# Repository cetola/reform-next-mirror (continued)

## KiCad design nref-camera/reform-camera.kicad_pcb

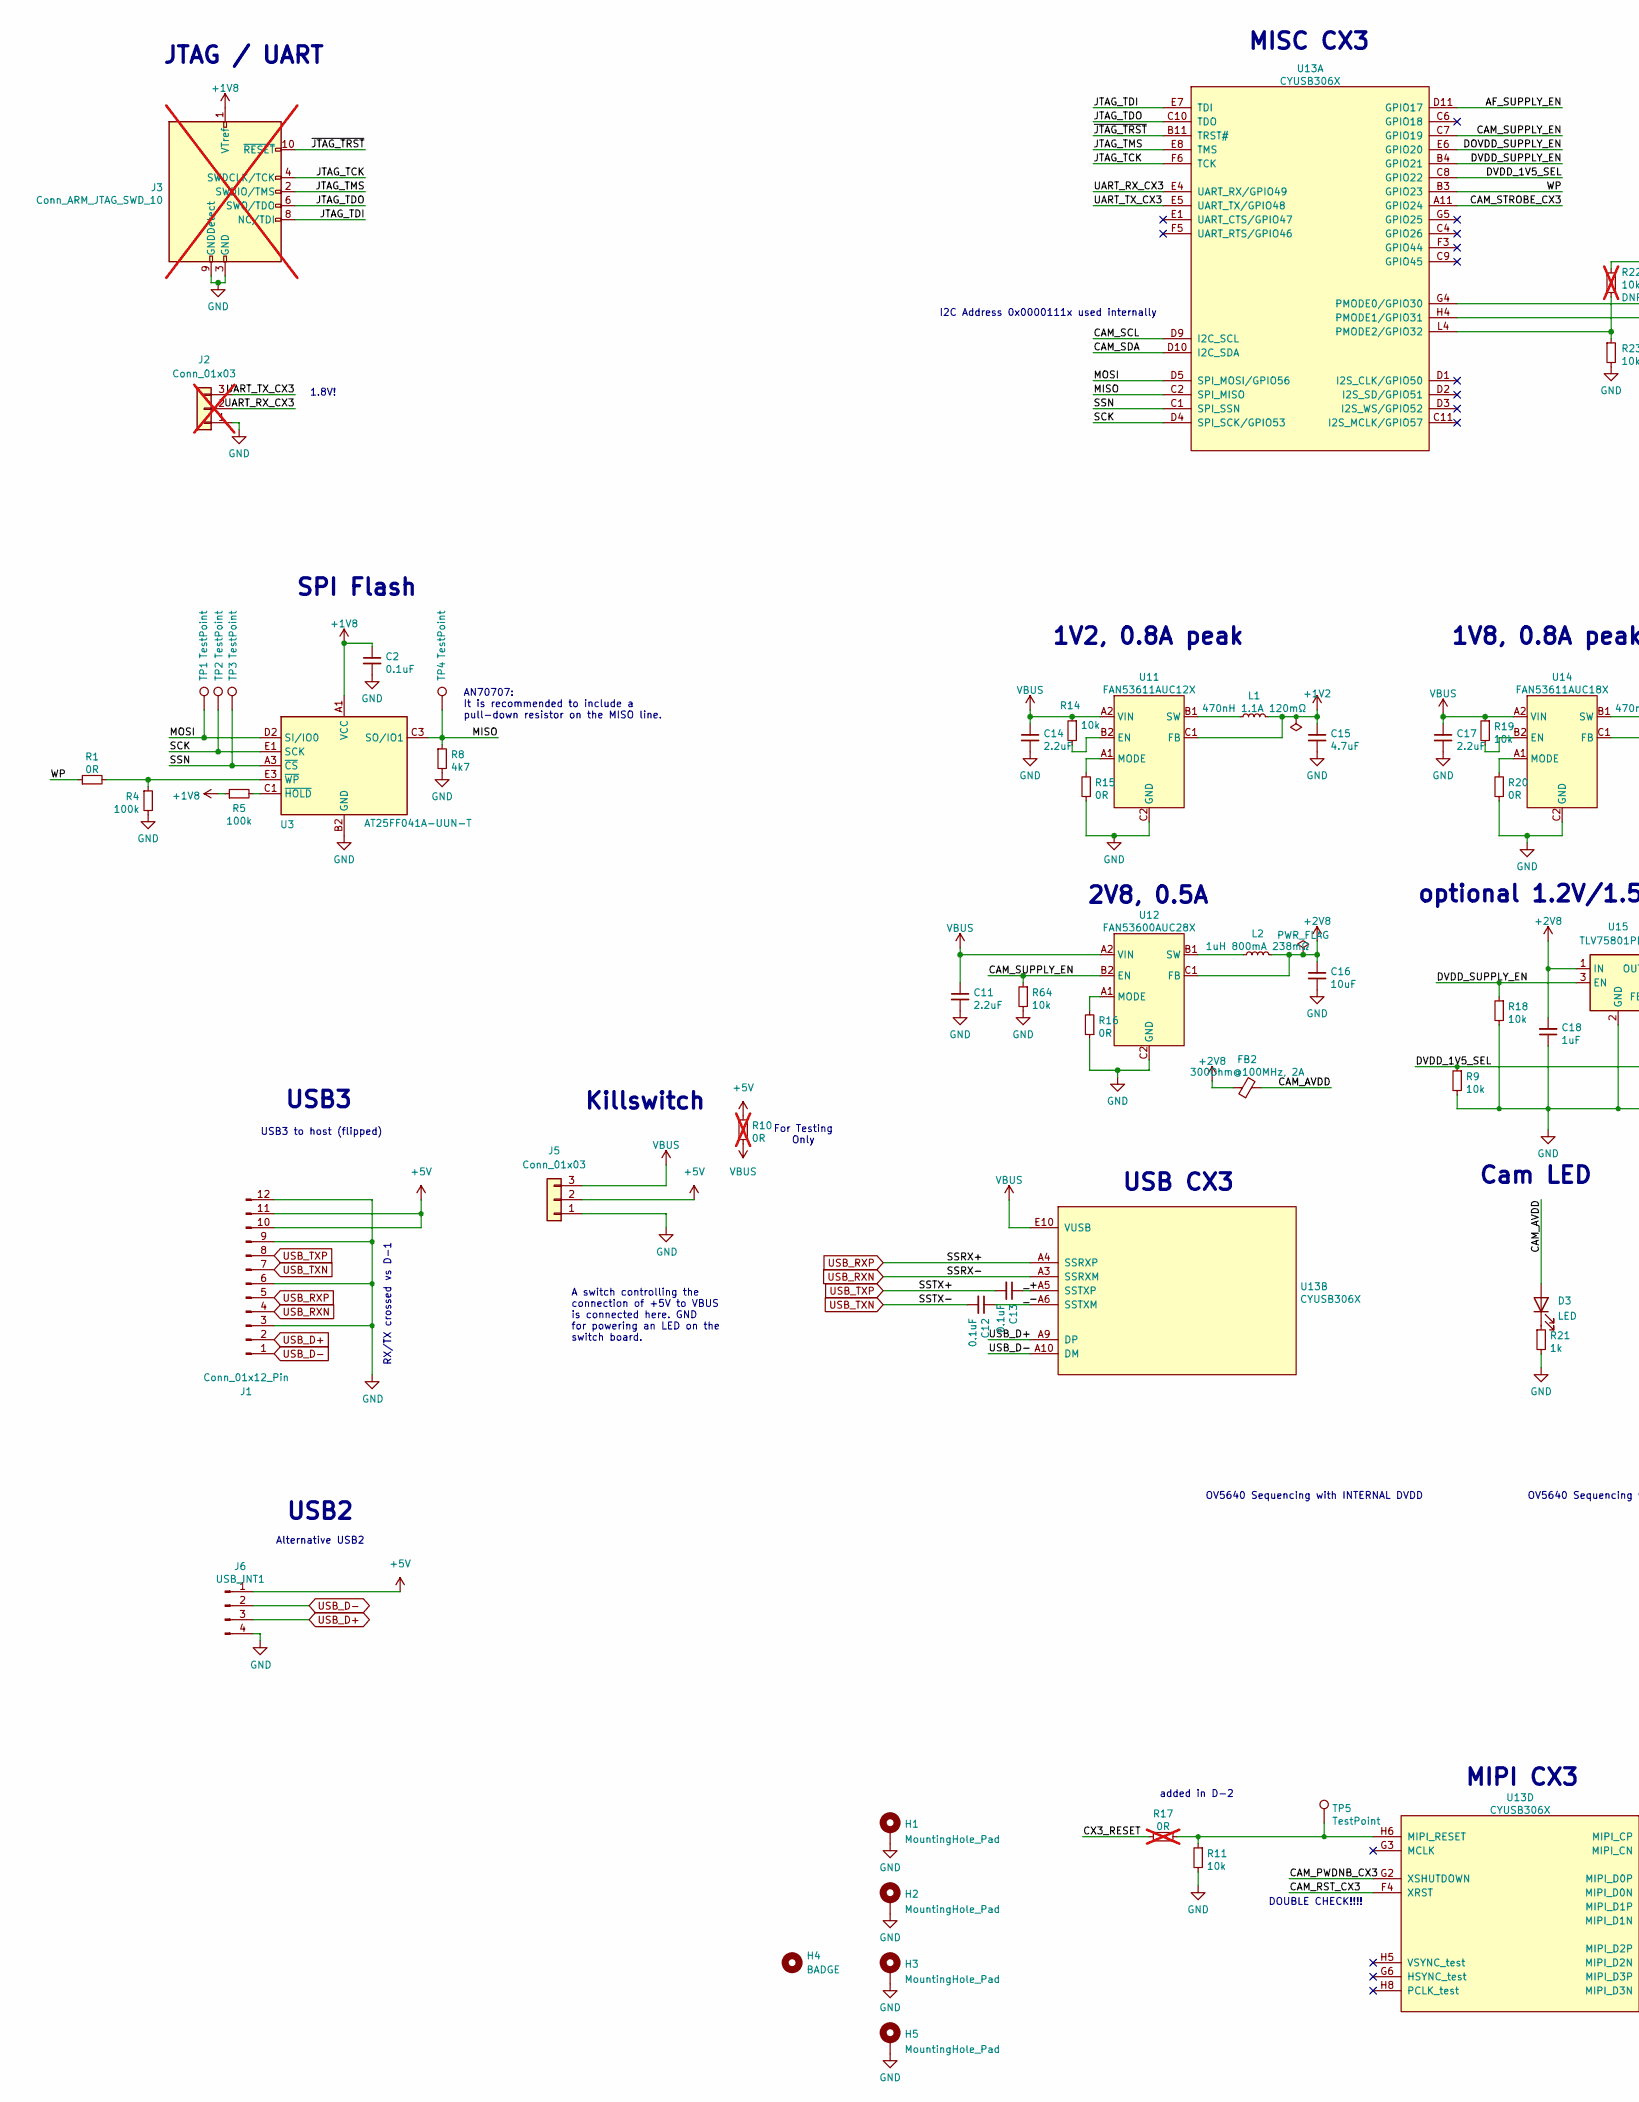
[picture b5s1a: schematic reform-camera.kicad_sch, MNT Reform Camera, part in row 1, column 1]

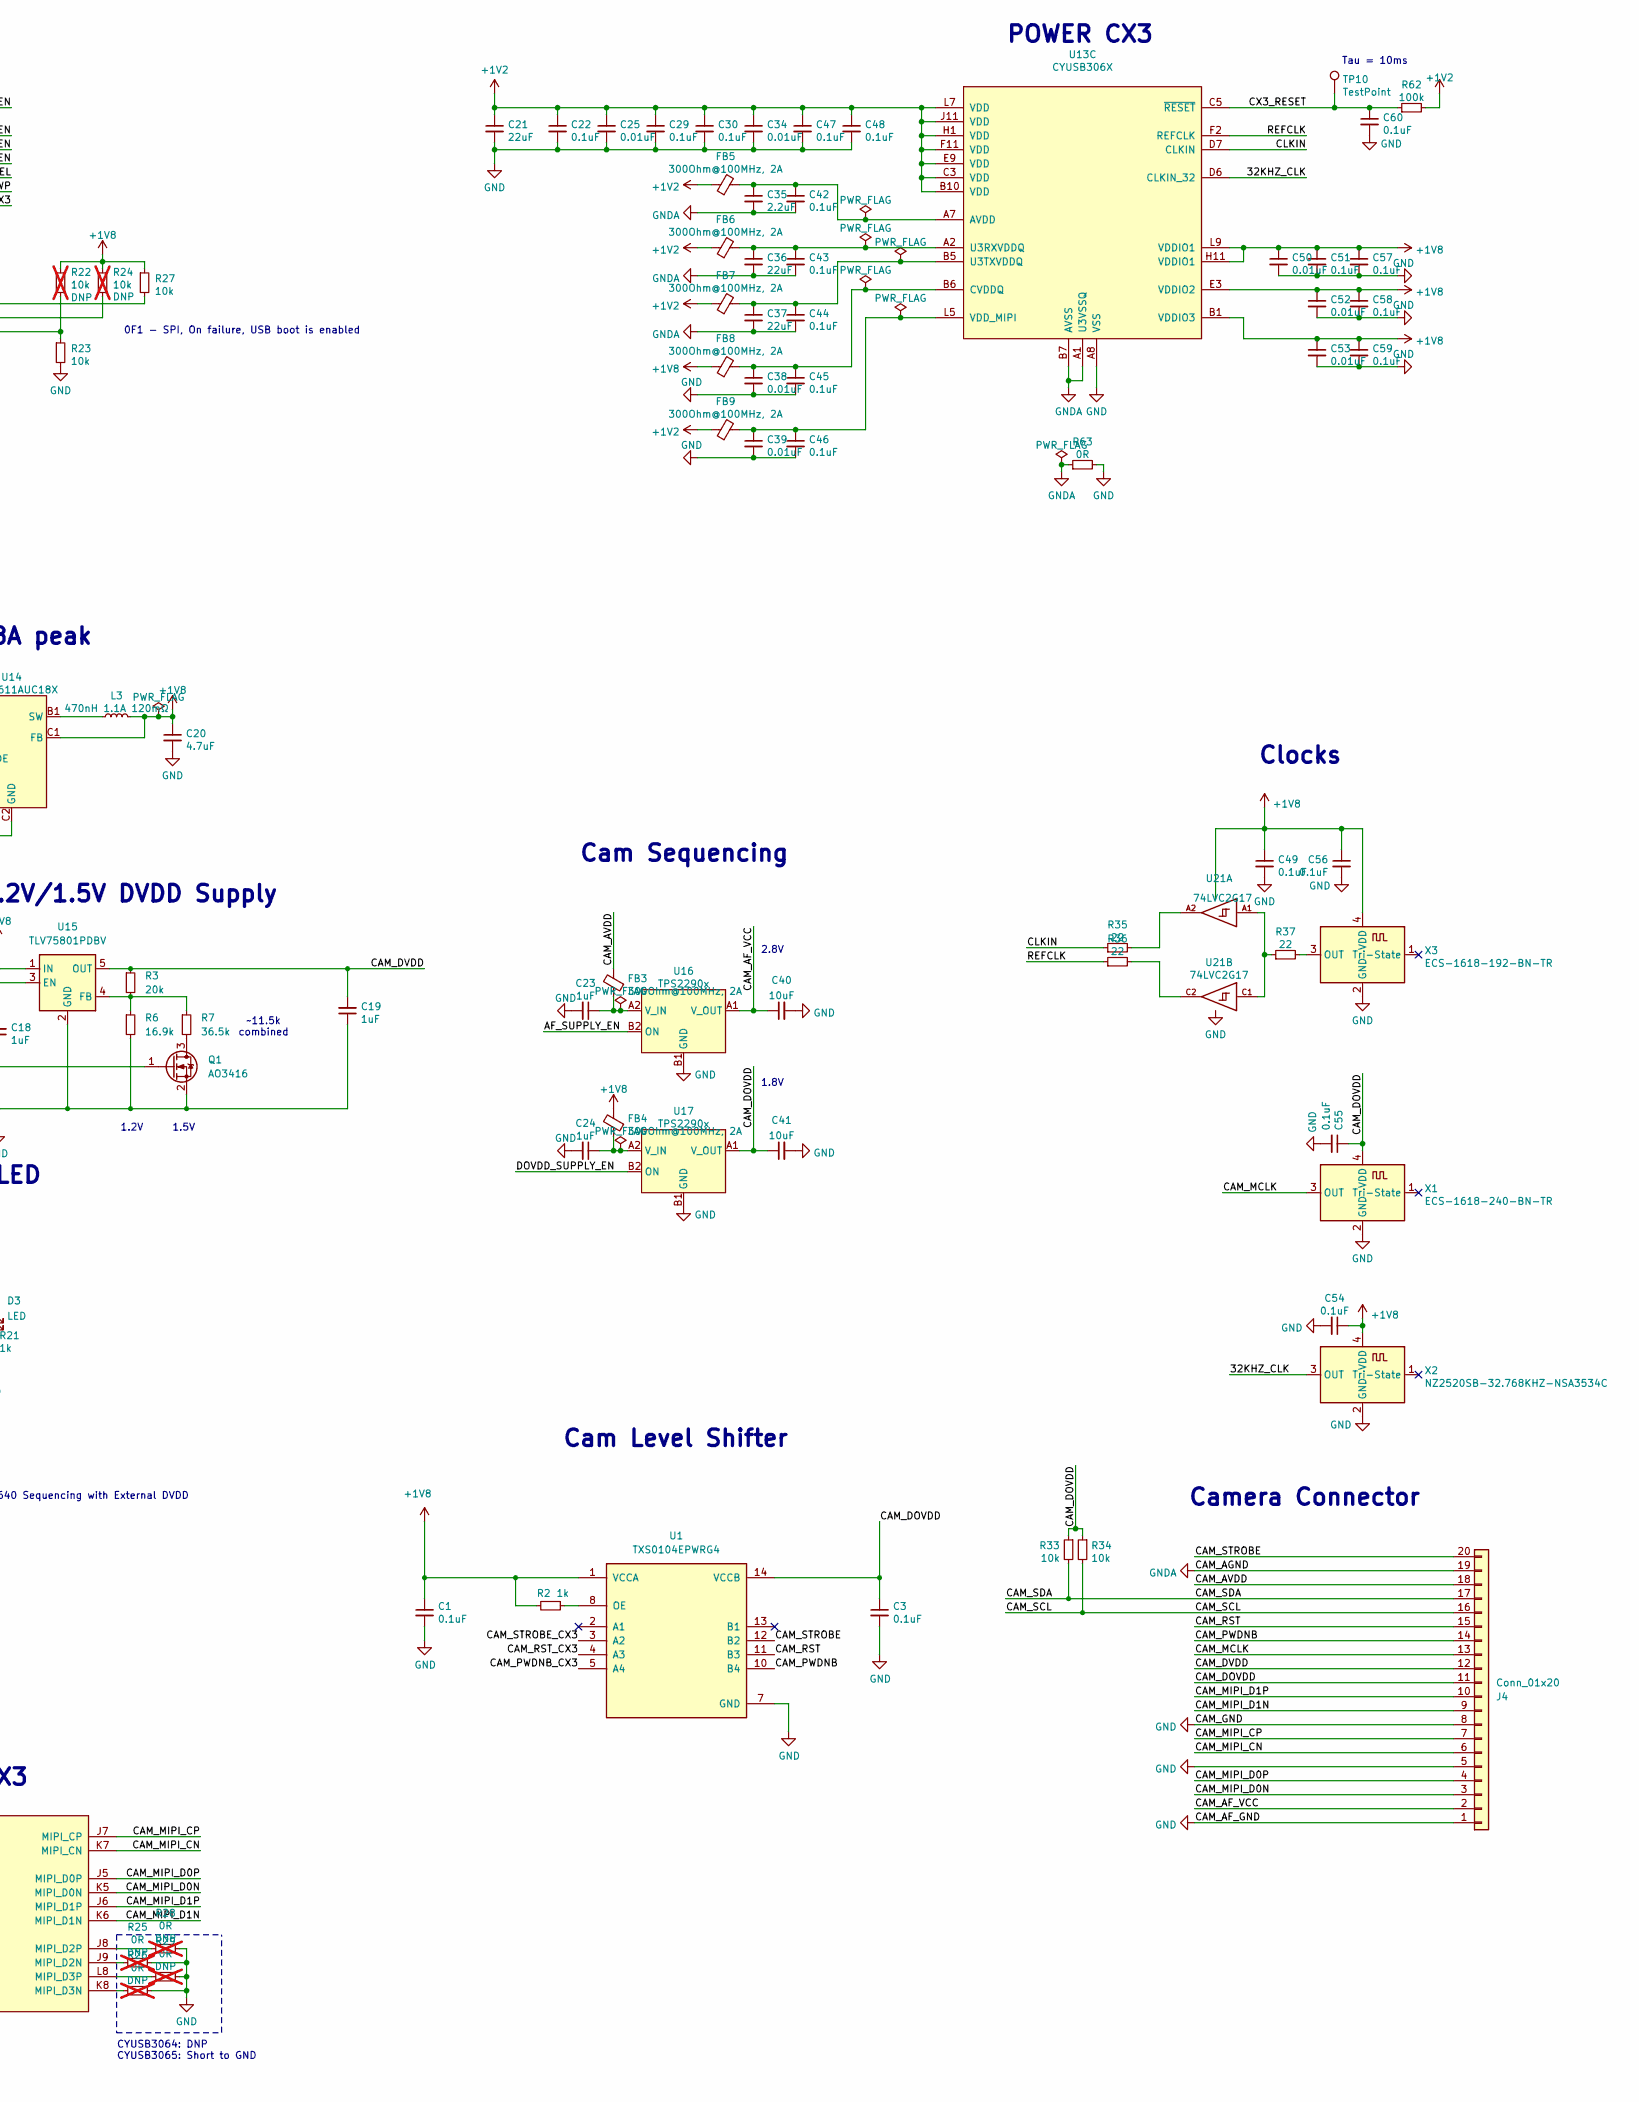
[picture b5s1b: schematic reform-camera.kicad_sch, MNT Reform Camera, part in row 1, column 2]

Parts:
C1, C3: 0.1uF; C_0402_1005Metric; MPN GRM155R71C104KA88J; LCSC C60474
C2, C12, C13, C22, C29, C30, C42, C43, C44, C45, C46, C47, C48, C49, C51, C54, C55, C56, C57, C58, C59, C60: 0.1uF; C_0402_1005Metric; MPN GRM155R71C104KA88J
C11, C14, C17, C35: 2.2uF; C_0402_1005Metric; MPN GRT155C81C225KE13D
C15, C20: 4.7uF; C_0402_1005Metric; MPN GRT155C81A475ME13J
C16, C40, C41: 10uF; C_0603_1608Metric; MPN C0603C106M8PAC7411
C18, C19, C23, C24: 1uF; C_0402_1005Metric; MPN GMK105CC6105KV-F
C21, C36, C37: 22uF; C_0603_1608Metric; MPN MSASJ168BC6226MTNA01
C25, C34, C38, C39, C50, C52, C53: 0.01uF; C_0402_1005Metric; MPN C0402C103K8RAC7411
D3: LED; LED_0603_1608Metric; MPN TLHR5400-AS12Z
FB2, FB3, FB4, FB5, FB6, FB7, FB8, FB9: 300Ohm@100MHz, 2A; C_0603_1608Metric; MPN MI0603L301R-10
H1, H2, H3, H5: MountingHole_Pad; MountingHole_2.2mm_M2_Pad; MPN DNP
H4: BADGE; nref-camera-badge; MPN DNP
J1: Conn_01x12_Pin; Hirose_FH12-12S-0.5SH_1x12-1MP_P0.50mm_Horizontal; MPN FH12-12S-0.5SH(55)
J2: Conn_01x03; PinSocket_1x03_P2.54mm_Vertical; MPN DNP; not fitted
J3: Conn_ARM_JTAG_SWD_10; PinHeader_2x05_P1.27mm_Vertical; MPN 62201021121 (DNP); not fitted
J4: Conn_01x20; JST_SH_SM20B-SRSS-TB_1x20-1MP_P1.00mm_Horizontal; MPN SM20B-SRSS-TB
J5: Conn_01x03; JST_SH_SM03B-SRSS-TB_1x03-1MP_P1.00mm_Horizontal; MPN SM03B-SRSS-TB
J6: USB_INT1; JST_SH_SM04B-SRSS-TB_1x04-1MP_P1.00mm_Horizontal; MPN SM04B-SRSS-TB; LCSC C160404
L1, L3: 470nH 1.1A 120mΩ; L_0805_2012Metric; MPN LQM21PNR47MC0D; Mouser 81-LQM21PNR47MC0D
L2: 1uH 800mA 238mΩ; L_0805_2012Metric; MPN LQM21PN1R0MC0D; Digikey 490-4992-1-ND
Q1: AO3416; SOT-23; MPN DMN2024U-7
R1, R15, R16, R20: 0R; R_0402_1005Metric; MPN CRCW04020000Z0EDC
R2, R21: 1k; R_0402_1005Metric; MPN CRCW04021K00FKEDC
R3: 20k; R_0402_1005Metric; MPN RC0402FR-7D20KL
R4, R5, R62: 100k; R_0402_1005Metric; MPN RC0402FR-07100KL
R6: 16.9k; R_0402_1005Metric; MPN CRCW040216K9FKTD
R7: 36.5k; R_0402_1005Metric; MPN RP0402BRD0736K5L
R8: 4k7; R_0402_1005Metric; MPN RC0402FR-074K7L
R9, R11, R14, R18, R19, R23, R27, R33, R34, R64: 10k; R_0402_1005Metric; MPN RC0402FR-7D10KL
R10, R17, R25, R26, R28, R29: 0R; R_0402_1005Metric; MPN CRCW04020000Z0EDC; not fitted
R22, R24: 10k; R_0402_1005Metric; MPN RC0402FR-7D10KL; not fitted
R35, R36, R37: 22; R_0402_1005Metric; MPN RC0402FR-7D22RL
R63: 0R; R_0603_1608Metric; MPN CRCW060320K0FKEAC
TP1, TP2, TP3, TP4, TP5, TP10: TestPoint; TestPoint_Pad_D0.7mm; MPN DNP
U1: TXS0104EPWRG4; SOP65P640X120-14N; MPN TXS0104EPWRG4
U3: AT25FF041A-UUN-T; WLCSP-8_1.58x1.63x0.35mm_Layout3x5_P0.35x0.4mm_Ball0.25mm_P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; MPN AT25FF041A-UUN-T
U11: FAN53611AUC12X; WLCSP-6_2x3_0.8x1.2mm; MPN FAN53611AUC12X
U12: FAN53600AUC28X; WLCSP-6_2x3_0.8x1.2mm; MPN FAN53600AUC28X
U13: CYUSB306X; XBGA-121_10x10mm_Layout11x11_P0.8mm; MPN CYUSB3064-BZXI
U14: FAN53611AUC18X; WLCSP-6_2x3_0.8x1.2mm; MPN FAN53611AUC18X
U15: TLV75801PDBV; SOT-23-5; MPN TLV75801PDBV
U16, U17: TPS2290x; Texas-DSBGA4_2x2_0.8x0.8mm_YFP; MPN TPS22902YFPR
U21: 74LVC2G17; Texas-DSBGA6_2x3_1.39x0.9mm_YZP; MPN SN74LVC2G17YZPR
X1: ECS-1618-240-BN-TR; ECS-1618; MPN ECS-1618-240-BN-TR
X2: NZ2520SB-32.768KHZ-NSA3534C; Crystal_SMD_EuroQuartz_X22-4Pin_2.5x2.0mm; MPN NZ2520SB-32.768KHZ-NSA3534C; Digikey 644-1197-2-ND
X3: ECS-1618-192-BN-TR; ECS-1618; MPN ECS-1618-192-BN-TR; Digikey XC1964CT-ND

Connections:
+1V2: C15.1, C21.1, C22.1, C25.1, C29.1, C30.1, C34.1, C47.1, C48.1, FB5.1, FB6.1, FB7.1, FB9.1, L1.2, R62.2, U11.C1 (FB), U13.B10 (VDD), U13.C3 (VDD), U13.E9 (VDD), U13.F11 (VDD), U13.H1 (VDD), U13.J11 (VDD), U13.L7 (VDD)
+1V8: C1.1, C2.1, C20.1, C49.1, C50.1, C51.1, C52.1, C53.1, C54.1, C56.1, C57.1, C58.1, C59.1, FB4.2, FB8.1, J3.1 (VTref), L3.2, R2.2, R5.1, R22.1, R24.1, R27.1, U1.1 (VCCA), U3.A1 (VCC), U13.B1 (VDDIO3), U13.E3 (VDDIO2), U13.H11 (VDDIO1), U13.L9 (VDDIO1), U14.C1 (FB), U21.B2 (VCC), X2.4 (VDD), X3.4 (VDD)
+2V8: C16.1, C18.2, FB2.1, L2.2, U12.C1 (FB), U15.1 (IN)
+5V: J1.10, J1.11, J5.2, J6.1, R10.2
/32KHZ_CLK: U13.D6 (CLKIN_32), X2.3 (OUT)
/AF_SUPPLY_EN: U13.D11 (GPIO17), U16.B2 (ON)
/CAM_AF_VCC: C40.1, J4.2, U16.A1 (V_OUT)
/CAM_AVDD: D3.2 (A), FB2.2, FB3.2, J4.18
/CAM_DOVDD: C3.1, C41.1, C55.1, J4.11, R33.1, R34.1, U1.14 (VCCB), U17.A1 (V_OUT), X1.4 (VDD)
/CAM_DVDD: C19.2, J4.12, R3.1, U15.5 (OUT)
/CAM_MCLK: J4.13, X1.3 (OUT)
/CAM_MIPI_CN: J4.6, U13.K7 (MIPI_CN)
/CAM_MIPI_CP: J4.7, U13.J7 (MIPI_CP)
/CAM_MIPI_D0N: J4.3, U13.K5 (MIPI_D0N)
/CAM_MIPI_D0P: J4.4, U13.J5 (MIPI_D0P)
/CAM_MIPI_D1N: J4.9, U13.K6 (MIPI_D1N)
/CAM_MIPI_D1P: J4.10, U13.J6 (MIPI_D1P)
/CAM_PWDNB: J4.14, U1.10 (B4)
/CAM_PWDNB_CX3: U1.5 (A4), U13.G2 (XSHUTDOWN)
/CAM_RST: J4.15, U1.11 (B3)
/CAM_RST_CX3: U1.4 (A3), U13.F4 (XRST)
/CAM_SCL: J4.16, R34.2, U13.D9 (I2C_SCL)
/CAM_SDA: J4.17, R33.2, U13.D10 (I2C_SDA)
/CAM_STROBE: J4.20, U1.12 (B2)
/CAM_STROBE_CX3: U1.3 (A2), U13.A11 (GPIO24)
/CAM_SUPPLY_EN: R64.1, U12.B2 (EN), U13.C7 (GPIO19)
/CLKIN: R35.1, U13.D7 (CLKIN)
/CX3_RESET: C60.1, R17.1, R62.1, TP10.1, U13.C5 (~RESET)
/DOVDD_SUPPLY_EN: U13.E6 (GPIO20), U17.B2 (ON)
/DVDD_1V5_SEL: Q1.1 (G), R9.1, U13.C8 (GPIO22)
/DVDD_SUPPLY_EN: R18.1, U13.B4 (GPIO21), U15.3 (EN)
/JTAG_TCK: J3.4 (SWDCLK/TCK), U13.F6 (TCK)
/JTAG_TDI: J3.8 (NC/TDI), U13.E7 (TDI)
/JTAG_TDO: J3.6 (SWO/TDO), U13.C10 (TDO)
/JTAG_TMS: J3.2 (SWDIO/TMS), U13.E8 (TMS)
/MISO: R8.1, TP4.1, U3.C3 (SO/IO1), U13.C2 (SPI_MISO)
/MOSI: TP1.1, U3.D2 (SI/IO0), U13.D5 (SPI_MOSI/GPIO56)
/REFCLK: R36.1, U13.F2 (REFCLK)
/SCK: TP2.1, U3.E1 (SCK), U13.D4 (SPI_SCK/GPIO53)
/SSN: TP3.1, U3.A3 (~CS), U13.C1 (SPI_SSN)
/UART_RX_CX3: J2.2, U13.E4 (UART_RX/GPIO49)
/UART_TX_CX3: J2.3, U13.E5 (UART_TX/GPIO48)
/WP: R1.1, U13.B3 (GPIO23)
/_+: C13.1, U13.A5 (SSTXP)
/_-: C12.1, U13.A6 (SSTXM)
/~JTAG_TRST: J3.10 (~RESET), U13.B11 (TRST#)
GND: C1.2, C2.2, C3.2, C11.2, C14.2, C15.2, C16.2, C17.2, C18.1, C19.1, C20.2, C21.2, C22.2, C23.2, C24.2, C25.2, C29.2, C30.2, C34.2, C38.2, C39.2, C40.2, C41.2, C45.2, C46.2, C47.2, C48.2, C49.2, C50.2, C51.2, C52.2, C53.2, C54.2, C55.2, C56.2, C57.2, C58.2, C59.2, C60.2, H1.1, H2.1, H3.1, H5.1, J1.3, J1.6, J1.9, J1.12, J2.1, J3.3 (GND), J3.5 (GND), J3.9 (GNDDetect), J4.1, J4.5, J4.8, J5.1, J6.4, Q1.2 (S), R4.2, R6.2, R8.2, R9.2, R11.2, R15.1, R16.1, R18.2, R20.1, R21.2, R23.2, R25.1, R26.1, R28.1, R29.1, R63.2, R64.2, U1.7 (GND), U3.B2 (GND), U11.C2 (GND), U12.C2 (GND), U13.A8 (VSS), U13.B2 (VSS), U13.B8 (VSS), U13.B9 (VSS), U13.D8 (VSS), U13.E2 (VSS), U13.E11 (VSS), U13.G1 (VSS), U13.G11 (VSS), U13.K3 (VSS), U13.K4 (VSS), U13.L1 (VSS), U13.L2 (VSS), U13.L3 (VSS), U13.L6 (VSS), U13.L11 (VSS), U14.C2 (GND), U15.2 (GND), U16.B1 (GND), U17.B1 (GND), U21.B1 (GND), X1.2 (GND), X2.2 (GND), X3.2 (GND)
GNDA: C35.2, C36.2, C37.2, C42.2, C43.2, C44.2, J4.19, R63.1, U13.A1 (U3VSSQ), U13.B7 (AVSS)
unnamed: D3.1 (K), R21.1
unnamed: Q1.3 (D), R7.2
unnamed: R35.2, U21.A2
unnamed: R36.2, U21.C2
unnamed: R37.1, U21.A1, U21.C1
unnamed: R2.1, U1.8 (OE)
unnamed: R5.2, U3.C1 (~HOLD)
unnamed: R1.2, R4.1, U3.E3 (~WP)
unnamed: R14.2, U11.B2 (EN)
unnamed: R15.2, U11.A1 (MODE)
unnamed: L1.1, U11.B1 (SW)
unnamed: R16.2, U12.A1 (MODE)
unnamed: L2.1, U12.B1 (SW)
unnamed: R27.2, U13.G4 (PMODE0/GPIO30)
unnamed: R24.2, U13.H4 (PMODE1/GPIO31)
unnamed: R22.2, R23.1, U13.L4 (PMODE2/GPIO32)
unnamed: C35.1, C42.1, FB5.2, U13.A7 (AVDD)
unnamed: C38.1, C45.1, FB8.2, U13.B6 (CVDDQ)
unnamed: C36.1, C43.1, FB6.2, U13.A2 (U3RXVDDQ)
unnamed: C37.1, C44.1, FB7.2, U13.B5 (U3TXVDDQ)
unnamed: C39.1, C46.1, FB9.2, U13.L5 (VDD_MIPI)
unnamed: R25.2, U13.J9 (MIPI_D2N)
unnamed: R28.2, U13.J8 (MIPI_D2P)
unnamed: R26.2, U13.K8 (MIPI_D3N)
unnamed: R29.2, U13.L8 (MIPI_D3P)
unnamed: R11.1, R17.2, TP5.1, U13.H6 (MIPI_RESET)
unnamed: R19.2, U14.B2 (EN)
unnamed: R20.2, U14.A1 (MODE)
unnamed: L3.1, U14.B1 (SW)
unnamed: R3.2, R6.1, R7.1, U15.4 (FB)
unnamed: C23.1, FB3.1, U16.A2 (V_IN)
unnamed: C24.1, FB4.1, U17.A2 (V_IN)
unnamed: R37.2, X3.3 (OUT)
USB_D+: J1.2, J6.3, U13.A9 (DP)
USB_D-: J1.1, J6.2, U13.A10 (DM)
USB_RXN: J1.4, U13.A3 (SSRXM)
USB_RXP: J1.5, U13.A4 (SSRXP)
USB_TXN: C12.2, J1.7
USB_TXP: C13.2, J1.8
VBUS: C11.1, C14.1, C17.1, J5.3, R10.1, R14.1, R19.1, U11.A2 (VIN), U12.A2 (VIN), U13.E10 (VUSB), U14.A2 (VIN)

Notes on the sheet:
Tau = 10ms
SPI Flash
added in D-2
Cam Level Shifter
OV5640 Sequencing with External DVDD
1V2, 0.8A peak
Clocks
1.2V
OV5640 Sequencing with INTERNAL DVDD
MISC CX3
2.8V
Cam Sequencing
1.8V
USB3
A switch controlling the connection of +5V to VBUS is connected here. GND for powering an LED on the switch board.
~11.5k combined
POWER CX3
Alternative USB2
AN70707: It is recommended to include a pull-down resistor on the MISO line.
optional 1.2V/1.5V DVDD Supply
0F1 - SPI, On failure, USB boot is enabled
I2C Address 0x0000111x used internally
JTAG / UART
CYUSB3064: DNP CYUSB3065: Short to GND
For Testing Only
Killswitch
1.8V!
RX/TX crossed vs D-1
2V8, 0.5A
DOUBLE CHECK!!!!
Cam LED
USB3 to host (flipped)
USB CX3
USB2
1.5V
Camera Connector
1V8, 0.8A peak
MIPI CX3

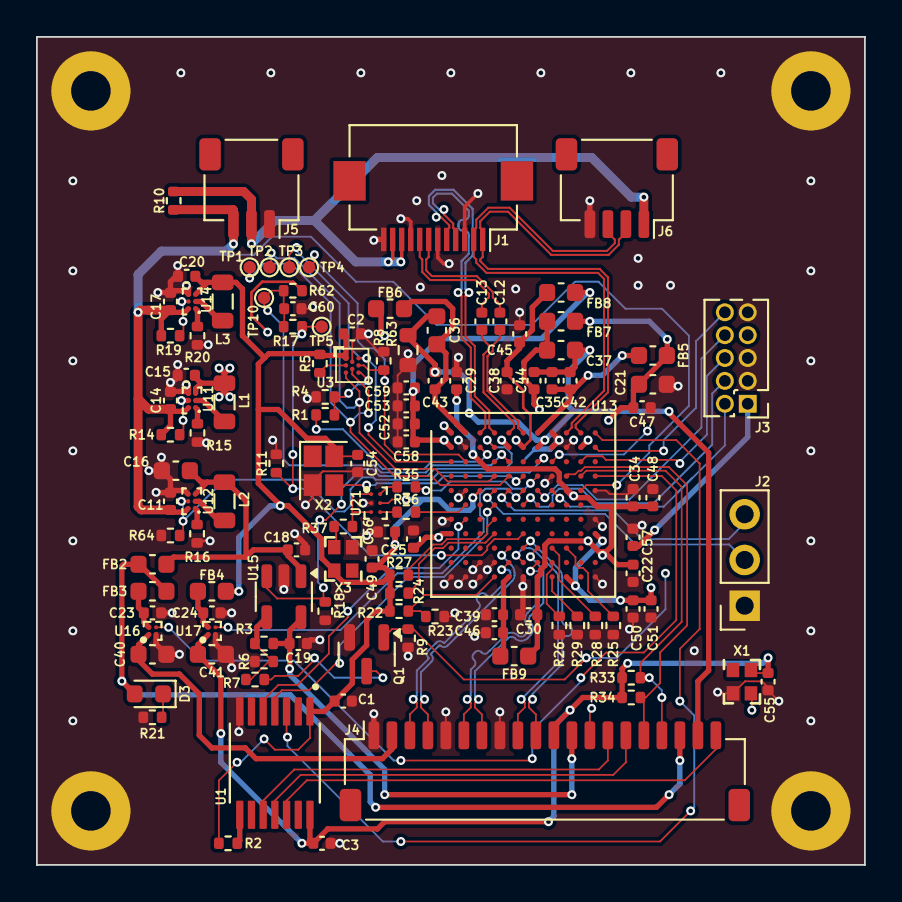
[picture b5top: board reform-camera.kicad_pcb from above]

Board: 4 copper layers, 46.0 x 46.0 mm, 125 parts (1 on the bottom side), 88 nets.

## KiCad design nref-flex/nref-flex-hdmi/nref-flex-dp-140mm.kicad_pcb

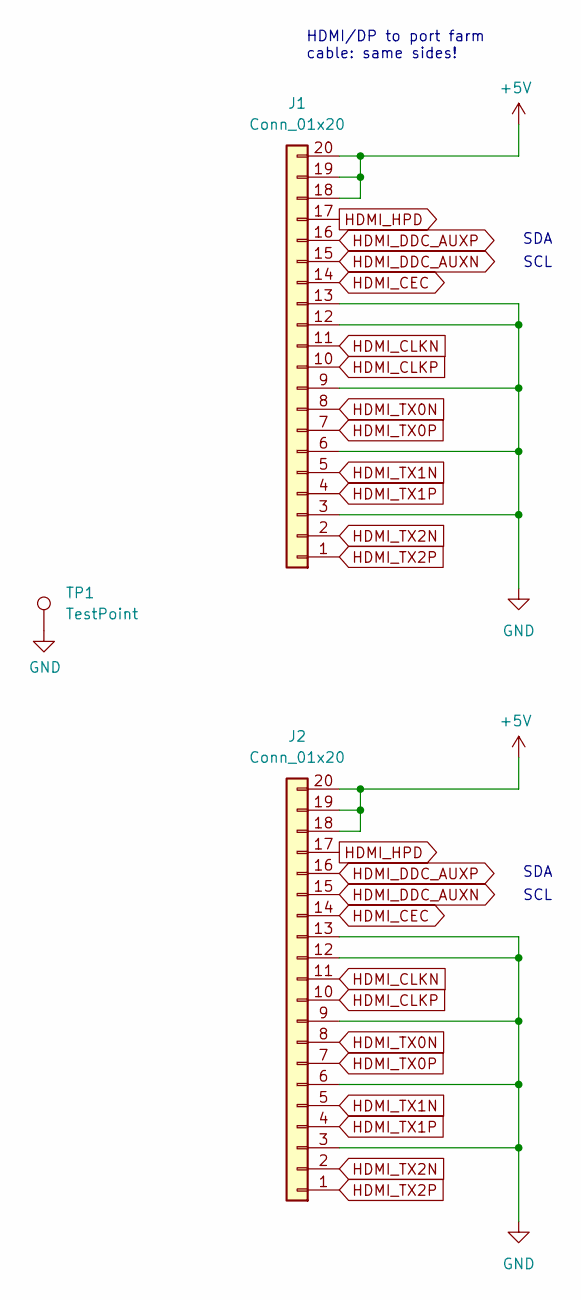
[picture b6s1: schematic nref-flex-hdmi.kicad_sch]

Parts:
J1, J2: Conn_01x20; Hirose_FH12-20S-0.5SH_1x20-1MP_P0.50mm_Horizontal
TP1: TestPoint; TestPoint_Pad_D1.0mm

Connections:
+5V: J1.18, J1.19, J1.20, J2.18, J2.19, J2.20
GND: J1.3, J1.6, J1.9, J1.12, J1.13, J2.3, J2.6, J2.9, J2.12, J2.13, TP1.1
HDMI_CEC: J1.14, J2.14
HDMI_CLKN: J1.11, J2.11
HDMI_CLKP: J1.10, J2.10
HDMI_DDC_AUXN: J1.15, J2.15
HDMI_DDC_AUXP: J1.16, J2.16
HDMI_HPD: J1.17, J2.17
HDMI_TX0N: J1.8, J2.8
HDMI_TX0P: J1.7, J2.7
HDMI_TX1N: J1.5, J2.5
HDMI_TX1P: J1.4, J2.4
HDMI_TX2N: J1.2, J2.2
HDMI_TX2P: J1.1, J2.1

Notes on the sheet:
SDA
SCL
HDMI/DP to port farm cable: same sides!

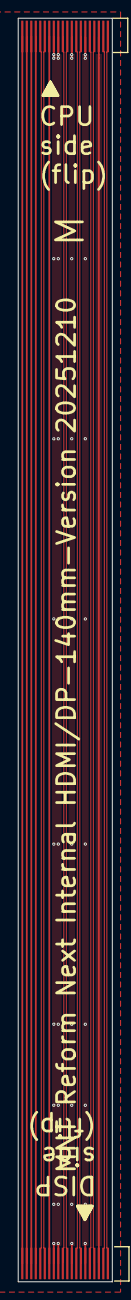
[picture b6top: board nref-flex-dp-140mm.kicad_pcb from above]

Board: 2 copper layers, 10.5 x 140.3 mm, 3 parts (1 on the bottom side), 14 nets.
